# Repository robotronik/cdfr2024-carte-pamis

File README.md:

# cdfr2024-carte-pamis
PCB pour PAMIS

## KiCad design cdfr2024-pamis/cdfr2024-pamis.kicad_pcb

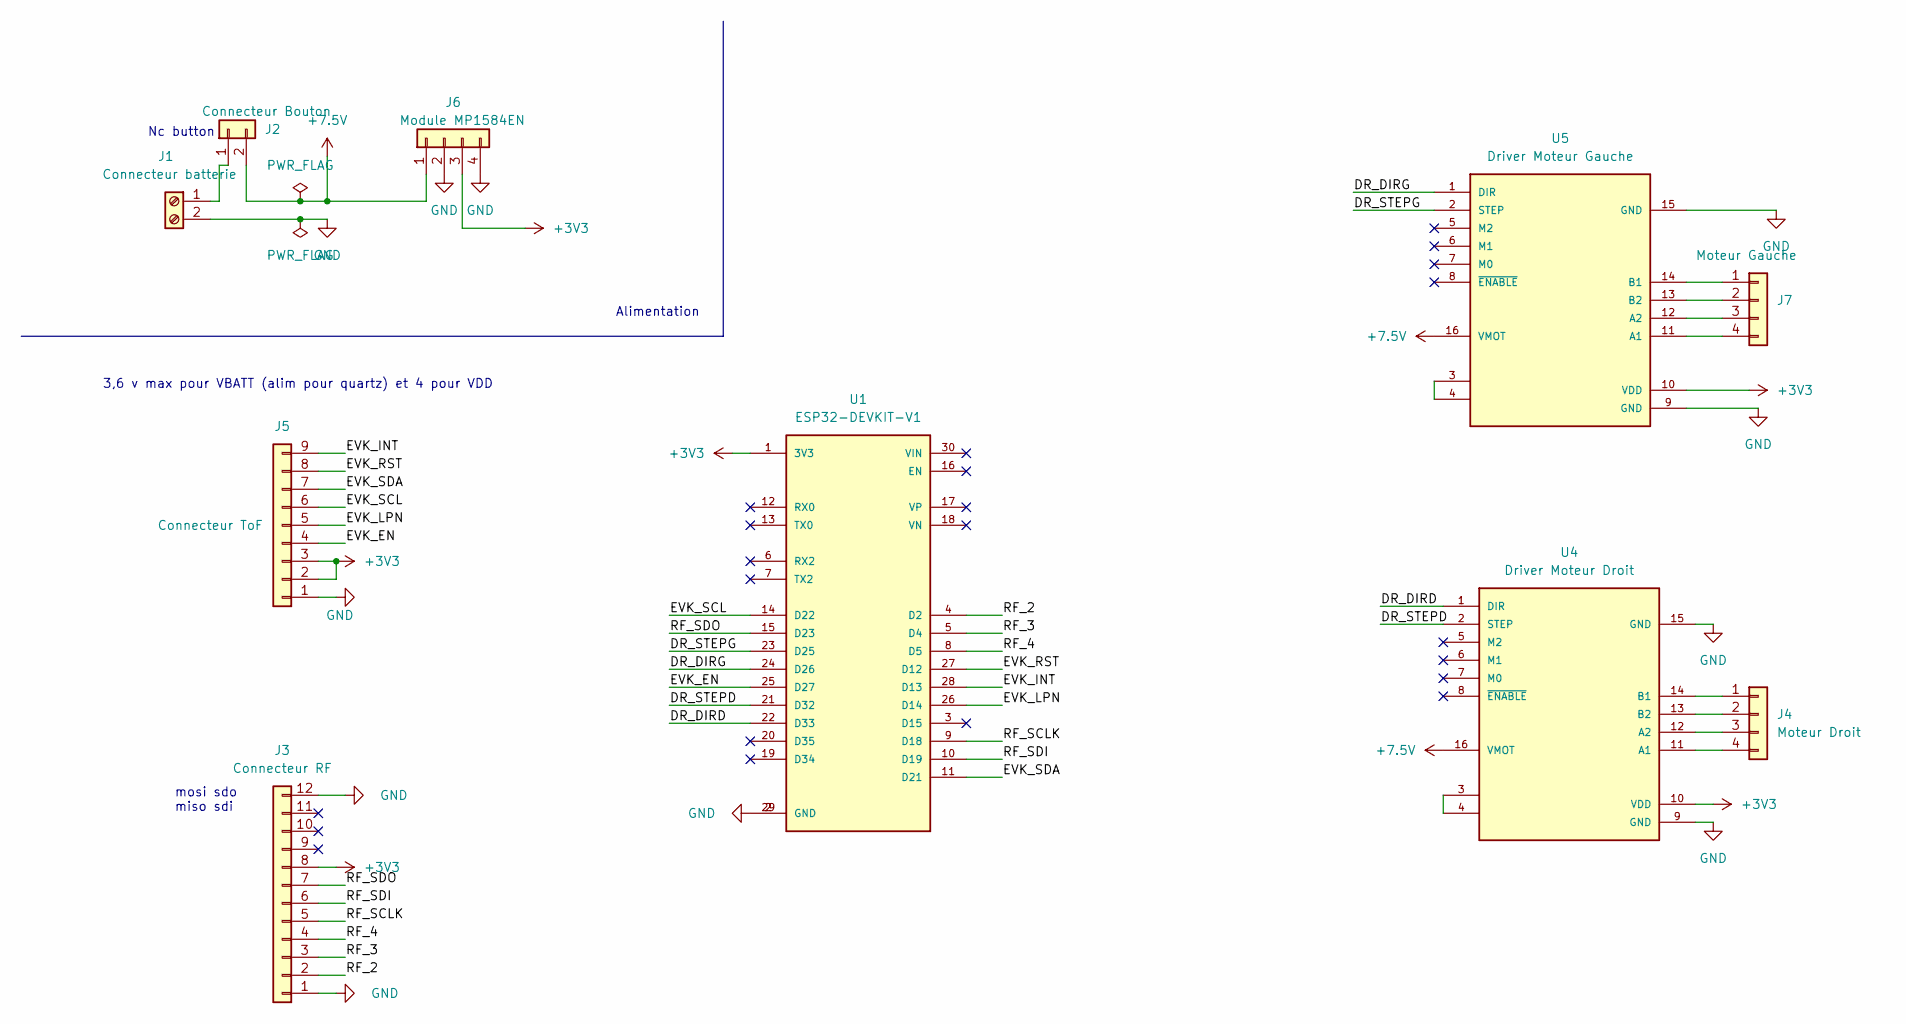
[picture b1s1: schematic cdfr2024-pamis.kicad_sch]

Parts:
J1: Connecteur batterie; CUI_TBP01R1-508-02BE
J2: Connecteur Bouton; PinHeader_1x02_P2.54mm_Vertical
J3: Connecteur RF; PinHeader_1x12_P2.54mm_Vertical
J4: Moteur Droit; PinHeader_1x04_P2.54mm_Vertical
J5: Connecteur ToF; PinHeader_1x09_P2.54mm_Vertical
J6: Module MP1584EN; SRT_MPT1584EN_Module
J7: Moteur Gauche; PinHeader_1x04_P2.54mm_Vertical
U1: ESP32-DEVKIT-V1; MODULE_ESP32_DEVKIT_V1; PARTREV N/A
U4: Driver Moteur Droit; MODULE_A4988_STEPPER_MOTOR_DRIVER_CARRIER
U5: Driver Moteur Gauche; MODULE_A4988_STEPPER_MOTOR_DRIVER_CARRIER

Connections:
+3V3: J3.8, J5.2, J5.3, J6.3, U1.1 (3V3), U4.10 (VDD), U5.10 (VDD)
+7.5V: J2.2, J6.1, U4.16 (VMOT), U5.16 (VMOT)
/DR_DIRD: U1.22 (D33), U4.1 (DIR)
/DR_DIRG: U1.24 (D26), U5.1 (DIR)
/DR_STEPD: U1.21 (D32), U4.2 (STEP)
/DR_STEPG: U1.23 (D25), U5.2 (STEP)
/EVK_EN: J5.4, U1.25 (D27)
/EVK_INT: J5.9, U1.28 (D13)
/EVK_LPN: J5.5, U1.26 (D14)
/EVK_RST: J5.8, U1.27 (D12)
/EVK_SCL: J5.6, U1.14 (D22)
/EVK_SDA: J5.7, U1.11 (D21)
/RF_2: J3.2, U1.4 (D2)
/RF_3: J3.3, U1.5 (D4)
/RF_4: J3.4, U1.8 (D5)
/RF_SCLK: J3.5, U1.9 (D18)
/RF_SDI: J3.6, U1.10 (D19)
/RF_SDO: J3.7, U1.15 (D23)
GND: J1.2, J3.1, J3.12, J5.1, J6.2, J6.4, U1.2 (GND), U1.29 (GND), U4.9 (GND), U4.15 (GND), U5.9 (GND), U5.15 (GND)
unnamed: J1.1, J2.1
unnamed: J4.1, U4.14 (B1)
unnamed: J4.2, U4.13 (B2)
unnamed: J4.3, U4.12 (A2)
unnamed: J4.4, U4.11 (A1)
unnamed: J7.1, U5.14 (B1)
unnamed: J7.2, U5.13 (B2)
unnamed: J7.3, U5.12 (A2)
unnamed: J7.4, U5.11 (A1)
unnamed: U4.3, U4.4
unnamed: U5.3, U5.4

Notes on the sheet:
Nc button
mosi sdo miso sdi
Alimentation
3,6 v max pour VBATT (alim pour quartz) et 4 pour VDD

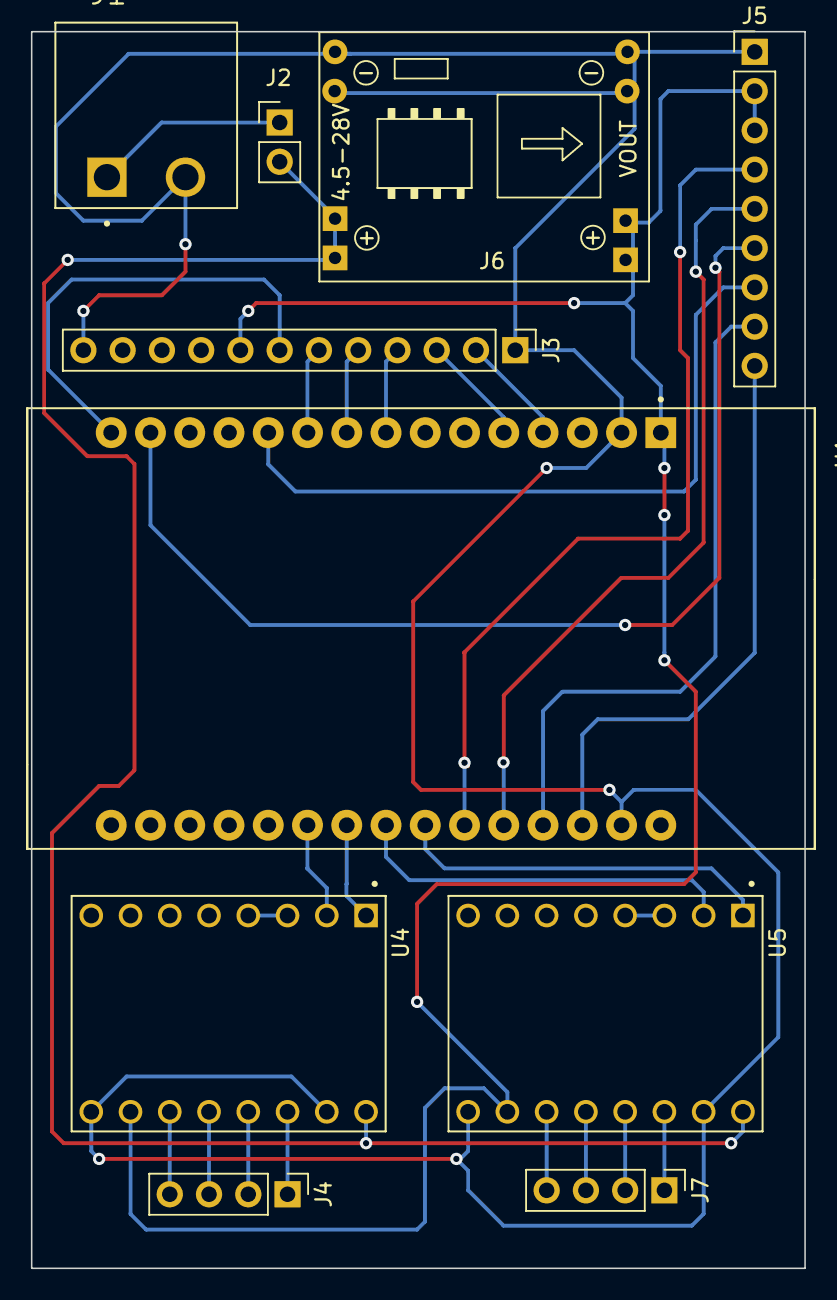
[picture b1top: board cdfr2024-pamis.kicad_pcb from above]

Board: 4 copper layers, 50.0 x 80.0 mm, 10 parts (0 on the bottom side), 30 nets.

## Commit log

2023-12-07 Schematic
2023-12-08 Refonte dossier
2023-12-19 - supression des messages d'erreur dans le schema - Suppression es message d'erreur sur PCB - modification des regles - modification du contour
2023-12-24 "Rapprochement capas 100nF + plan de masse + tous de fixation"
2023-12-26 changement de sens connecteur alim IN
2024-01-10 Change via sizes, only through vias
2024-01-10 Resize vias again
2024-01-10 Remove lock file, sorry
2024-02-22 datasheet
2024-02-23 module wifi
2024-02-27 Routage + DRC
2024-03-21 carte fablab module rf
2024-03-26 Adjustments for useless pins
2024-03-28 carte pamis
